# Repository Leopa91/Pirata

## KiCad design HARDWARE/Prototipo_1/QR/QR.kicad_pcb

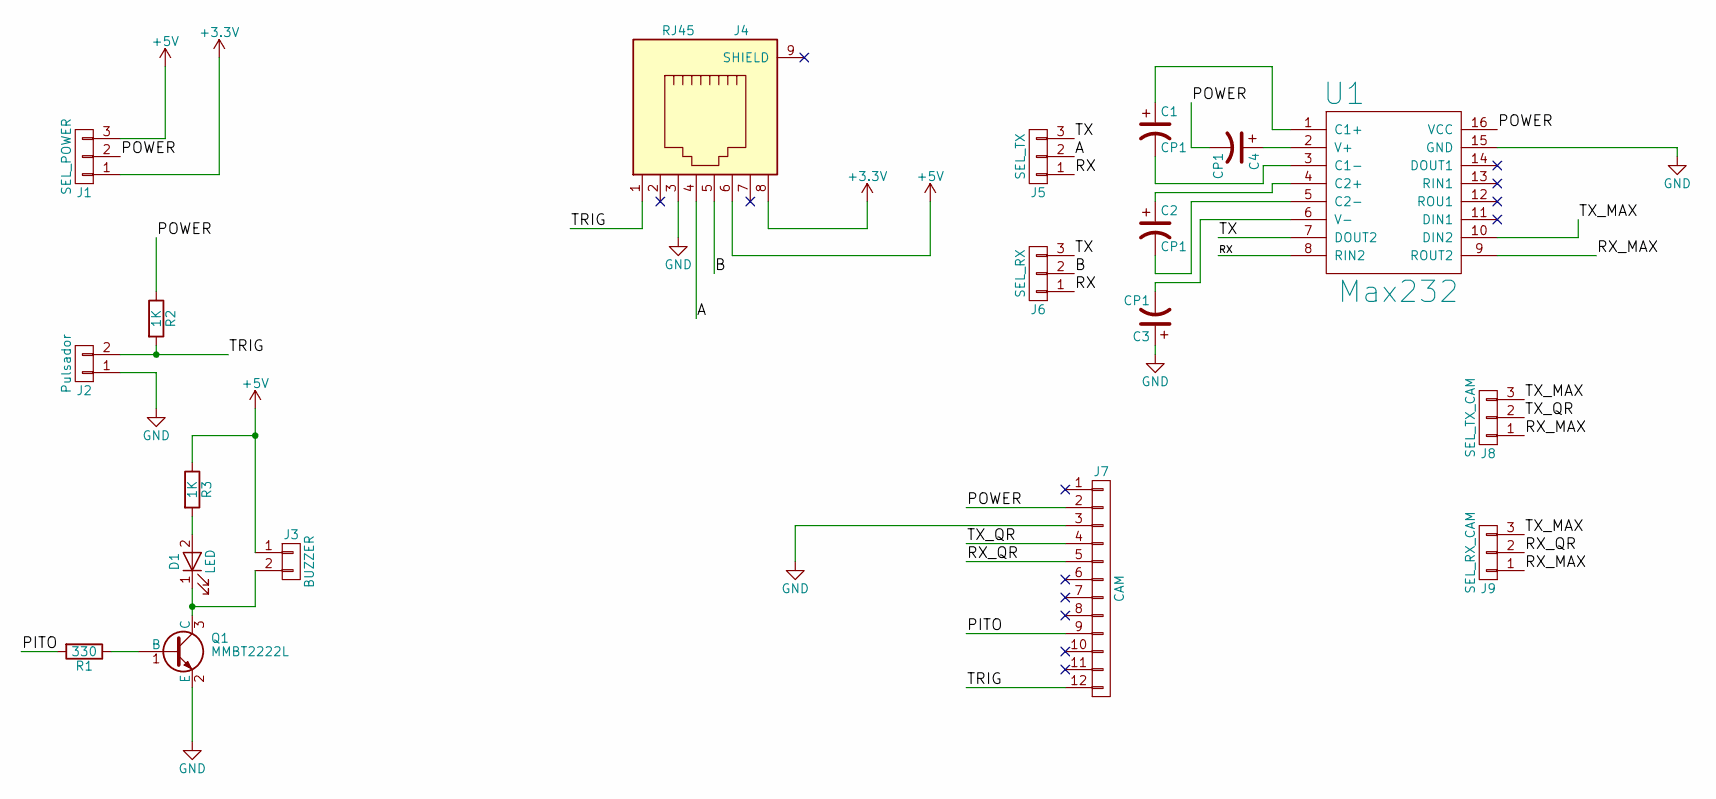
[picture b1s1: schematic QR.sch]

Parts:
C1, C2, C3, C4: CP1; C_0603_HandSoldering
D1: LED; LED_0603
J1: SEL_POWER; Socket_Strip_Straight_1x03_Pitch2.54mm
J2: Pulsador; Socket_Strip_Straight_1x02_Pitch2.54mm
J3: BUZZER; Socket_Strip_Straight_1x02_Pitch2.54mm
J4: RJ45; 8p8c-RJ45
J5: SEL_TX; Socket_Strip_Straight_1x03_Pitch2.54mm
J6: SEL_RX; Socket_Strip_Straight_1x03_Pitch2.54mm
J7: CAM; WR-FPC
J8: SEL_TX_CAM; Socket_Strip_Straight_1x03_Pitch2.54mm
J9: SEL_RX_CAM; Socket_Strip_Straight_1x03_Pitch2.54mm
Q1: MMBT2222L; SOT-23_Handsoldering
R1: 330; R_0603_HandSoldering
R2, R3: 1K; R_0603_HandSoldering
U1: Max232; SOIC-16_3.9x9.9mm_Pitch1.27mm

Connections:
+3V3: J1.1, J4.8
+5V: J1.3, J3.1, J4.6, R3.1
/A: J4.4, J5.2
/B: J4.5, J6.2
/PITO: J7.9, R1.2
/POWER: C4.2, J1.2, J7.2, R2.1, U1.16 (VCC)
/RX: J5.1, J6.1, U1.8 (RIN2)
/RX_MAX: J8.1, J9.1, U1.9 (ROUT2)
/RX_QR: J7.5, J9.2
/TRIG: J2.2, J4.1, J7.12, R2.2
/TX: J5.3, J6.3, U1.7 (DOUT2)
/TX_MAX: J8.3, J9.3, U1.10 (DIN2)
/TX_QR: J7.4, J8.2
GND: C3.1, J2.1, J4.3, J7.3, Q1.2 (E), U1.15 (GND)
unnamed: C1.1, U1.1 (C1+)
unnamed: C1.2, U1.3 (C1-)
unnamed: C2.1, U1.4 (C2+)
unnamed: C2.2, U1.5 (C2-)
unnamed: C3.2, U1.6 (V-)
unnamed: C4.1, U1.2 (V+)
unnamed: D1.1 (K), J3.2, Q1.3 (C)
unnamed: D1.2 (A), R3.2
unnamed: Q1.1 (B), R1.1

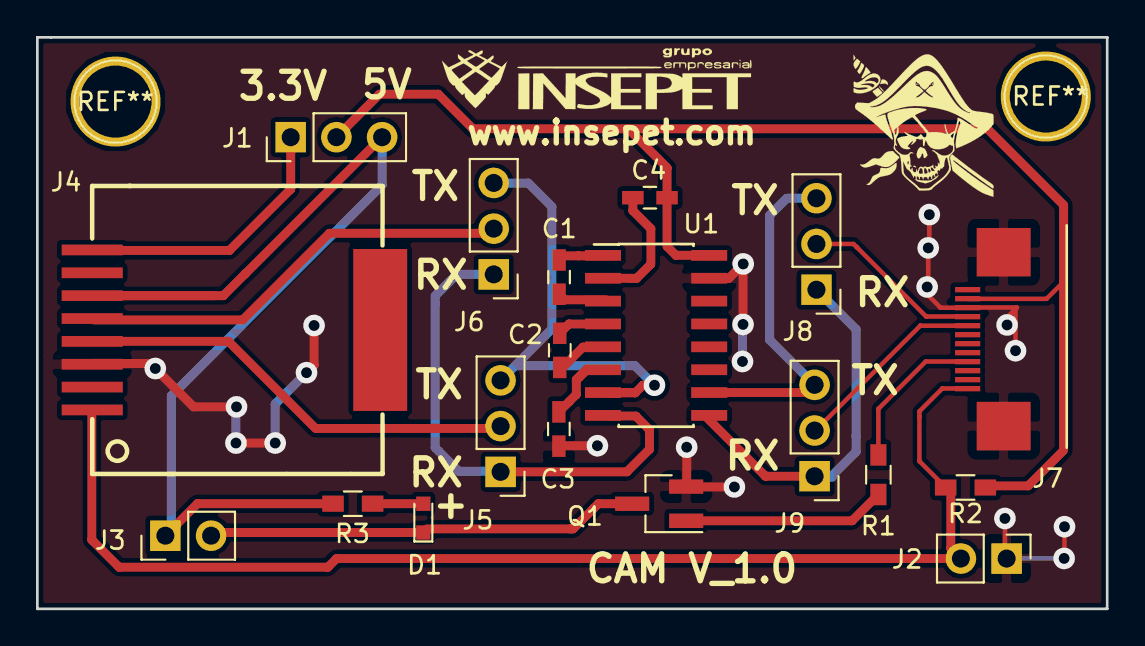
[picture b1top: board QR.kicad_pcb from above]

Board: 2 copper layers, 59.4 x 31.7 mm, 20 parts (0 on the bottom side), 23 nets.

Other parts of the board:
www.insepet.com: LOGO; Insepet

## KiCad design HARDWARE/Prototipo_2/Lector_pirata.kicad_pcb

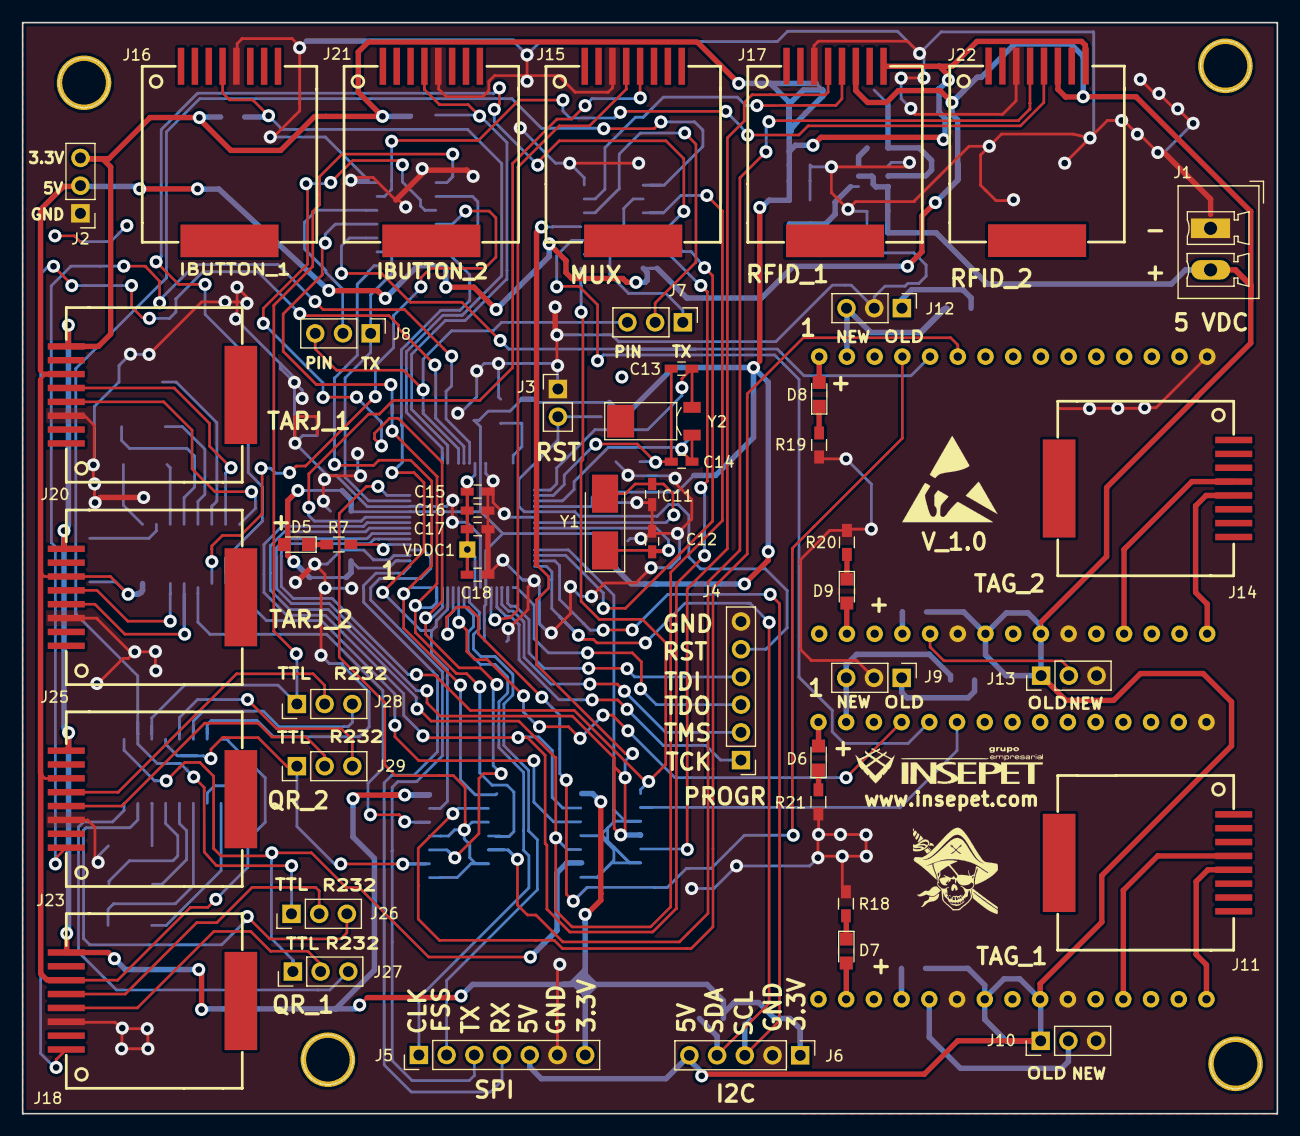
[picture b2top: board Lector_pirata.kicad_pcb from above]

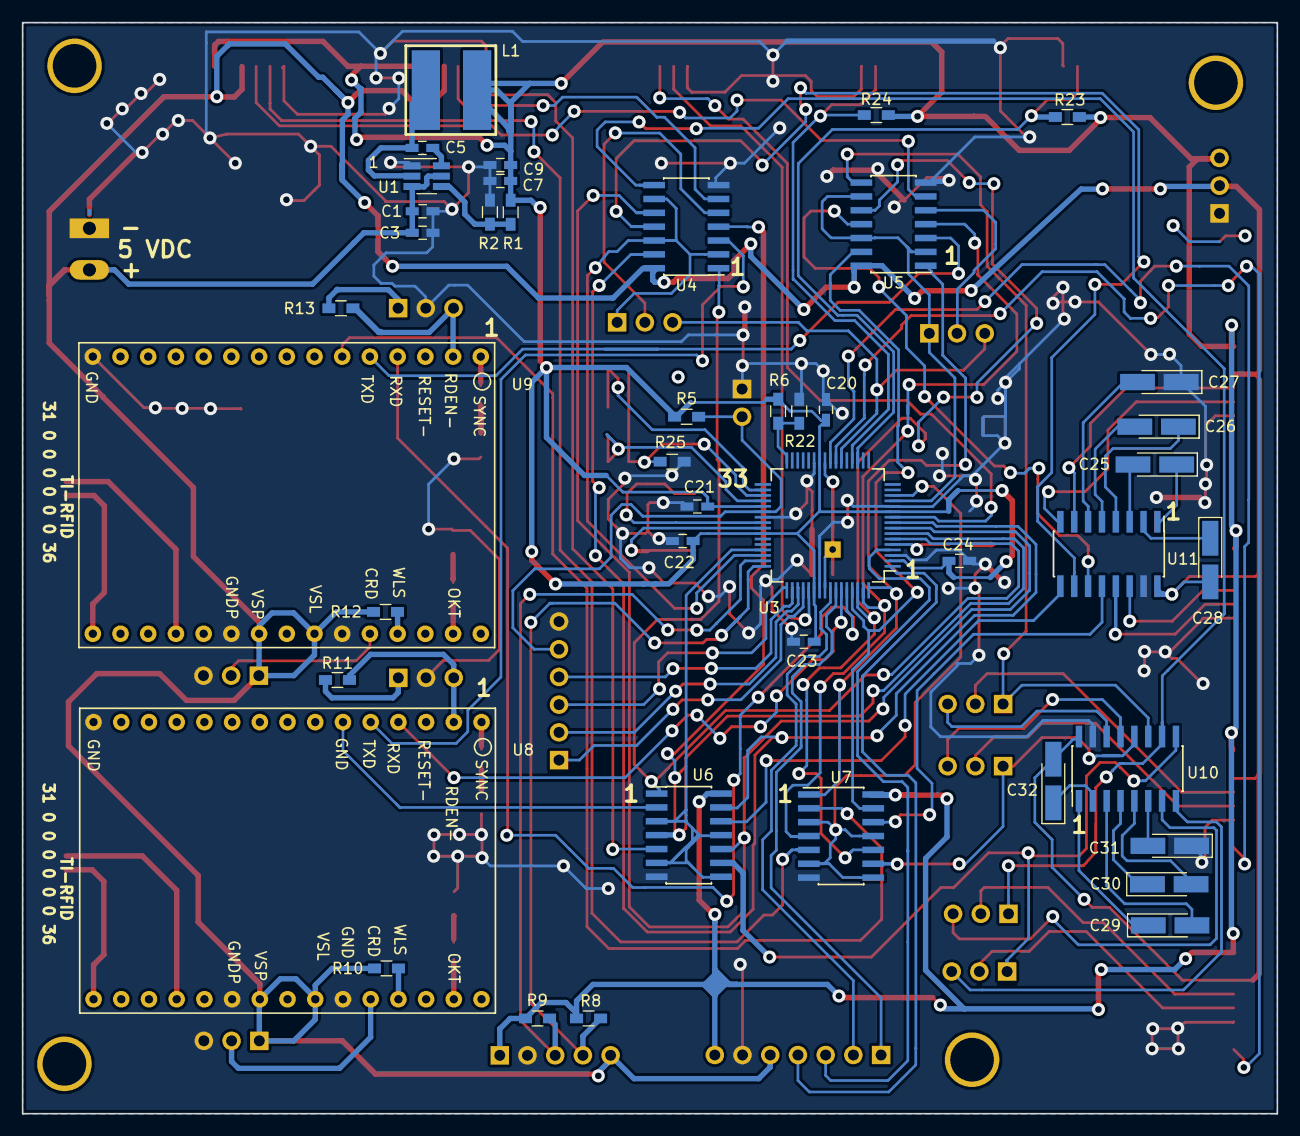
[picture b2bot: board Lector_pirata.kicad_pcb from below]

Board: 2 copper layers, 115.0 x 100.0 mm, 93 parts (43 on the bottom side), 109 nets.

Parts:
C1, C3: 10uF; C_0603_HandSoldering
C5, C17, C18, C20, C22: 0.1uF; C_0603_HandSoldering
C7, C9: 22uF; C_0603_HandSoldering
C11, C12: 10pF; C_0603_HandSoldering
C13, C14: 24pF; C_0603_HandSoldering
C15: 2.2uF; C_0603_HandSoldering
C16: 1.uF; C_0603_HandSoldering
C21, C23: 0.01uF; C_0603_HandSoldering
C24: 1uF; C_0603_HandSoldering
C25, C26, C27, C28, C29, C30, C31, C32: 0.1uF; CP_Tantalum_Case-A_EIA-3216-18_Hand
D5, D6, D7, D8, D9: LED; LED_0805
J1: CONN_01X02; PhoenixContact_MCV-G_02x5.08mm_Vertical
J2: test Poins; Pin_Header_Straight_1x03_Pitch2.54mm
J3: RESET; Pin_Header_Straight_1x02_Pitch2.54mm
J4: CONN_01X06; Pin_Header_Straight_1x06_Pitch2.54mm
J5: CONN_01X07; Pin_Header_Straight_1x07_Pitch2.54mm
J6: CONN_01X05; Pin_Header_Straight_1x05_Pitch2.54mm
J7, J8, J28, J29: CONN_01X03; Pin_Header_Straight_1x03_Pitch2.54mm
J9, J10, J12, J13: PIN_3; Pin_Header_Straight_1x03_Pitch2.54mm
J11, J14, J15, J16, J17, J18, J20, J21, J22, J23, J25: RJ45; 8p8c-RJ45
J26: QR_1; Pin_Header_Straight_1x03_Pitch2.54mm
J27: QR_2; Pin_Header_Straight_1x03_Pitch2.54mm
L1: 3.3uH; SRR6038-3R3Y
Logo: ESD-Logo_8.9x8mm_SilkScreen
R1: 33.2K; R_0603_HandSoldering
R2, R5, R10, R12: 10K; R_0603_HandSoldering
R6: 1M; R_0603_HandSoldering
R7: 1K; R_0603_HandSoldering
R8, R9: 4.7K; R_0603_HandSoldering
R11, R13: 33K; R_0603_HandSoldering
R18, R19, R20, R21: 330; R_0603_HandSoldering
R22, R25: 0; R_0603_HandSoldering
R23, R24: 5K; R_0603_HandSoldering
U1: TPS5622; SOT-23-6_Handsoldering
U3: TM4C1231H6PM; LQFP-64_10x10mm_Pitch0.5mm
U4, U5, U6, U7: 74HC125; SOIC-14_3.9x8.7mm_Pitch1.27mm
U8, U9: Microreader
U10, U11: Max232; SOIC-16_3.9x9.9mm_Pitch1.27mm
VDDC1: CONN_01X01; 1pin
Y1: 16MHz; Crystal_SMD_5032-2pin_5.0x3.2mm_HandSoldering
Y2: Crystal; Crystal_SMD_FrontierElectronics_FM206
www.insepet.com: LOGO; Insepet

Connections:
+3V3: C7.1, C9.1, C20.1, C21.1, C22.1, C23.1, C24.1, D5.2, J2.3, J5.7, J6.1, J17.8, J18.8, J20.8, J22.8, J23.8, J25.8, L1.2, R1.1, R5.1, R6.2, R8.1, R9.1, R23.2, R24.1, U3.2, U3.11, U3.26, U3.37, U3.42, U3.54, U6.14, U7.14
+5V: C1.2, C3.1, C28.2, C32.2, J1.2, J2.2, J5.5, J6.5, J10.1, J13.1, J17.6, J18.6, J20.6, J22.6, J23.6, J25.6, R10.2, R12.2, U1.3, U1.5, U4.14, U5.14, U8.22, U8.24, U9.22, U9.24, U10.16, U11.16
/Conectores/QR_RX_1_MAX: J27.3, U10.8
/Conectores/QR_RX_2_MAX: J29.3, U10.13
/Conectores/QR_TX_1_MAX: J26.3, U10.7
/Conectores/QR_TX_2_MAX: J28.3, U10.14
/Conectores/RX_QR_1: J18.4, J27.2
/Conectores/RX_QR_2: J23.4, J29.2
/Conectores/TX_QR_1: J18.5, J26.2
/Conectores/TX_QR_2: J23.5, J28.2
/Microread/ANT1: J11.5, U8.16
/Microread/ANT1_2: J14.5, U9.16
/Microread/ANT2: J11.4, U8.19
/Microread/ANT2_2: J14.4, U9.19
/Microread/CRMD: J10.2, U8.26
/Microread/CRMD_2: J13.2, U9.26
/Microread/OKT: D7.2, U8.29
/Microread/OKT_2: D9.2, U9.29
/Microread/RDEN-: J9.3, R11.1, U8.2
/Microread/RDEN-_2: J12.3, R13.1, U9.2
/Microread/SYNC: D6.2, U8.1
/Microread/SYNC_2: D8.2, U9.1
/Microread/WLS: R10.1, U8.27
/Microread/WLS_2: R12.1, U9.27
/RS-232/2A: J7.2, U4.5
/RS-232/2A_TX: J8.2, U5.5
/TM4C1231H6PM/CLK: J5.1, U3.58
/TM4C1231H6PM/FSS: J5.2, U3.57
/TM4C1231H6PM/GNDX: C13.2, C14.1, R25.1, U3.35
/TM4C1231H6PM/I1C_SCL: J6.3, R9.2, U3.47
/TM4C1231H6PM/I2C_SDA: J6.4, R8.2, U3.48
/TM4C1231H6PM/RST: J3.2, J4.5, R5.2, U3.38
/TM4C1231H6PM/RX: J5.4, U3.1
/TM4C1231H6PM/TCK: J4.1, U3.52
/TM4C1231H6PM/TDI: J4.4, U3.50
/TM4C1231H6PM/TDO: J4.3, U3.49
/TM4C1231H6PM/TMS: J4.2, U3.51
/TM4C1231H6PM/TX: J5.3, U3.4
AUX_1: J7.3, J8.3, U3.22
GND: C1.1, C3.2, C7.2, C9.2, C11.2, C12.2, C15.2, C16.2, C17.2, C18.2, C20.2, C21.2, C22.2, C23.2, C24.2, C27.1, C31.1, J1.1, J2.1, J3.1, J4.6, J5.6, J6.2, J9.2, J10.3, J12.2, J13.3, J15.3, J16.5, J17.3, J18.3, J20.3, J21.5, J22.3, J23.3, J25.3, R2.2, R18.2, R19.2, R20.2, R21.2, R22.1, R25.2, U1.1, U3.3, U3.12, U3.27, U3.39, U3.55, U4.7, U5.7, U6.7, U7.7, U8.15, U8.21, U8.25, U9.15, U9.21, U9.25, U10.15, U11.15
unnamed: C5.1, L1.1, U1.2
unnamed: C5.2, U1.6
unnamed: C11.1, U3.40, Y1.2
unnamed: C12.1, U3.41, Y1.1
unnamed: C13.1, U3.34, Y2.1
unnamed: C14.2, U3.36, Y2.2
unnamed: C15.1, C16.1, C17.1, C18.1, U3.25, U3.56, VDDC1.1
unnamed: C25.1, U11.1
unnamed: C25.2, U11.3
unnamed: C26.1, U11.4
unnamed: C26.2, U11.5
unnamed: C27.2, U11.6
unnamed: C28.1, U11.2
unnamed: C29.1, U10.1
unnamed: C29.2, U10.3
unnamed: C30.1, U10.4
unnamed: C30.2, U10.5
unnamed: C31.2, U10.6
unnamed: C32.1, U10.2
unnamed: D5.1, R7.2
unnamed: D6.1, R21.1
unnamed: D7.1, R18.1
unnamed: D8.1, R19.1
unnamed: D9.1, R20.1
unnamed: J9.1, R11.2
unnamed: J12.1, R13.2
unnamed: J20.4, U11.8
unnamed: J20.5, U11.7
unnamed: J25.4, U11.13
unnamed: J25.5, U11.14
unnamed: R1.2, R2.1, U1.4
unnamed: R7.1, U3.5
unnamed: R6.1, R22.2, U3.32
ONE_WIRE_1: J16.4, R23.1, U3.19
ONE_WIRE_2: J21.4, R24.2, U3.20
QR_RX_1: J27.1, U6.9, U10.9
QR_RX_2: J29.1, U7.9, U10.12
QR_TX_1: J26.1, U4.8, U10.10
QR_TX_2: J28.1, U5.8, U10.11
REST_TAG_1: U3.59, U8.4
REST_TAG_2: U3.60, U9.4
RFID_RX_1: J17.4, U6.5
RFID_RX_2: J22.4, U7.5
RFID_TX_1: J17.5, U4.6
RFID_TX_2: J22.5, U5.6
SEL_QR: U3.8, U4.10, U6.10
SEL_QR_2: U3.62, U5.10, U7.10
SEL_RFID: U3.7, U4.4, U6.4
SEL_RFID_2: U3.63, U5.4, U7.4
SEL_TAG: U3.6, U4.1, U6.1
SEL_TAG_2: U3.64, U5.1, U7.1
SEL_TAR: U3.9, U4.13, U6.13
SEL_TAR_2: U3.61, U5.13, U7.13
TAG_RX_1: U6.2, U8.6
TAG_RX_2: U7.2, U9.6
TAG_TX_1: U4.3, U8.5
TAG_TX_2: U5.3, U9.5
TAR_RX_1: U6.12, U11.9
TAR_RX_2: U7.12, U11.12
TAR_TX_1: U4.11, U11.10
TAR_TX_2: U5.11, U11.11
TRIG_1: J18.1, U3.23
TRIG_2: J23.1, U3.24
UART0_TX: J7.1, U3.46, U4.2, U4.9, U4.12
UART1_TX: J8.1, U3.13, U5.2, U5.9, U5.12
USART0_RX: U3.45, U6.3, U6.6, U6.8, U6.11
USART1_RX: U3.14, U7.3, U7.6, U7.8, U7.11
USART2_RX: J15.4, U3.53
USART2_TX: J15.5, U3.10

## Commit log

2017-08-28 version_4
